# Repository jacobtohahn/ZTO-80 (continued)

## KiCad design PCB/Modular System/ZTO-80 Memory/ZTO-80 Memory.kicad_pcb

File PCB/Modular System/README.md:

## Modular System PCBs
The subfolders in this directory contain the KiCad project files and additional files for Modular System boards. Look in each subfolder for information on each board and files.

## Component Notes
Unless stated otherwise in a README or silkscreen, always use CMOS ICs to build your system.

To bridge jumpers, I recommend using standard 0.1 in. jumper shunts.

Please note that the 40-pin bus header uses a non-standard PCB footprint in my designs. This is to keep compatability with my older designs, which used the same footprint. The footprint still works with standard headers and isn't an issue unless you are making your own designs. To use this footprint, see the PCB design in the "ZTO-80 Template" subfolder.

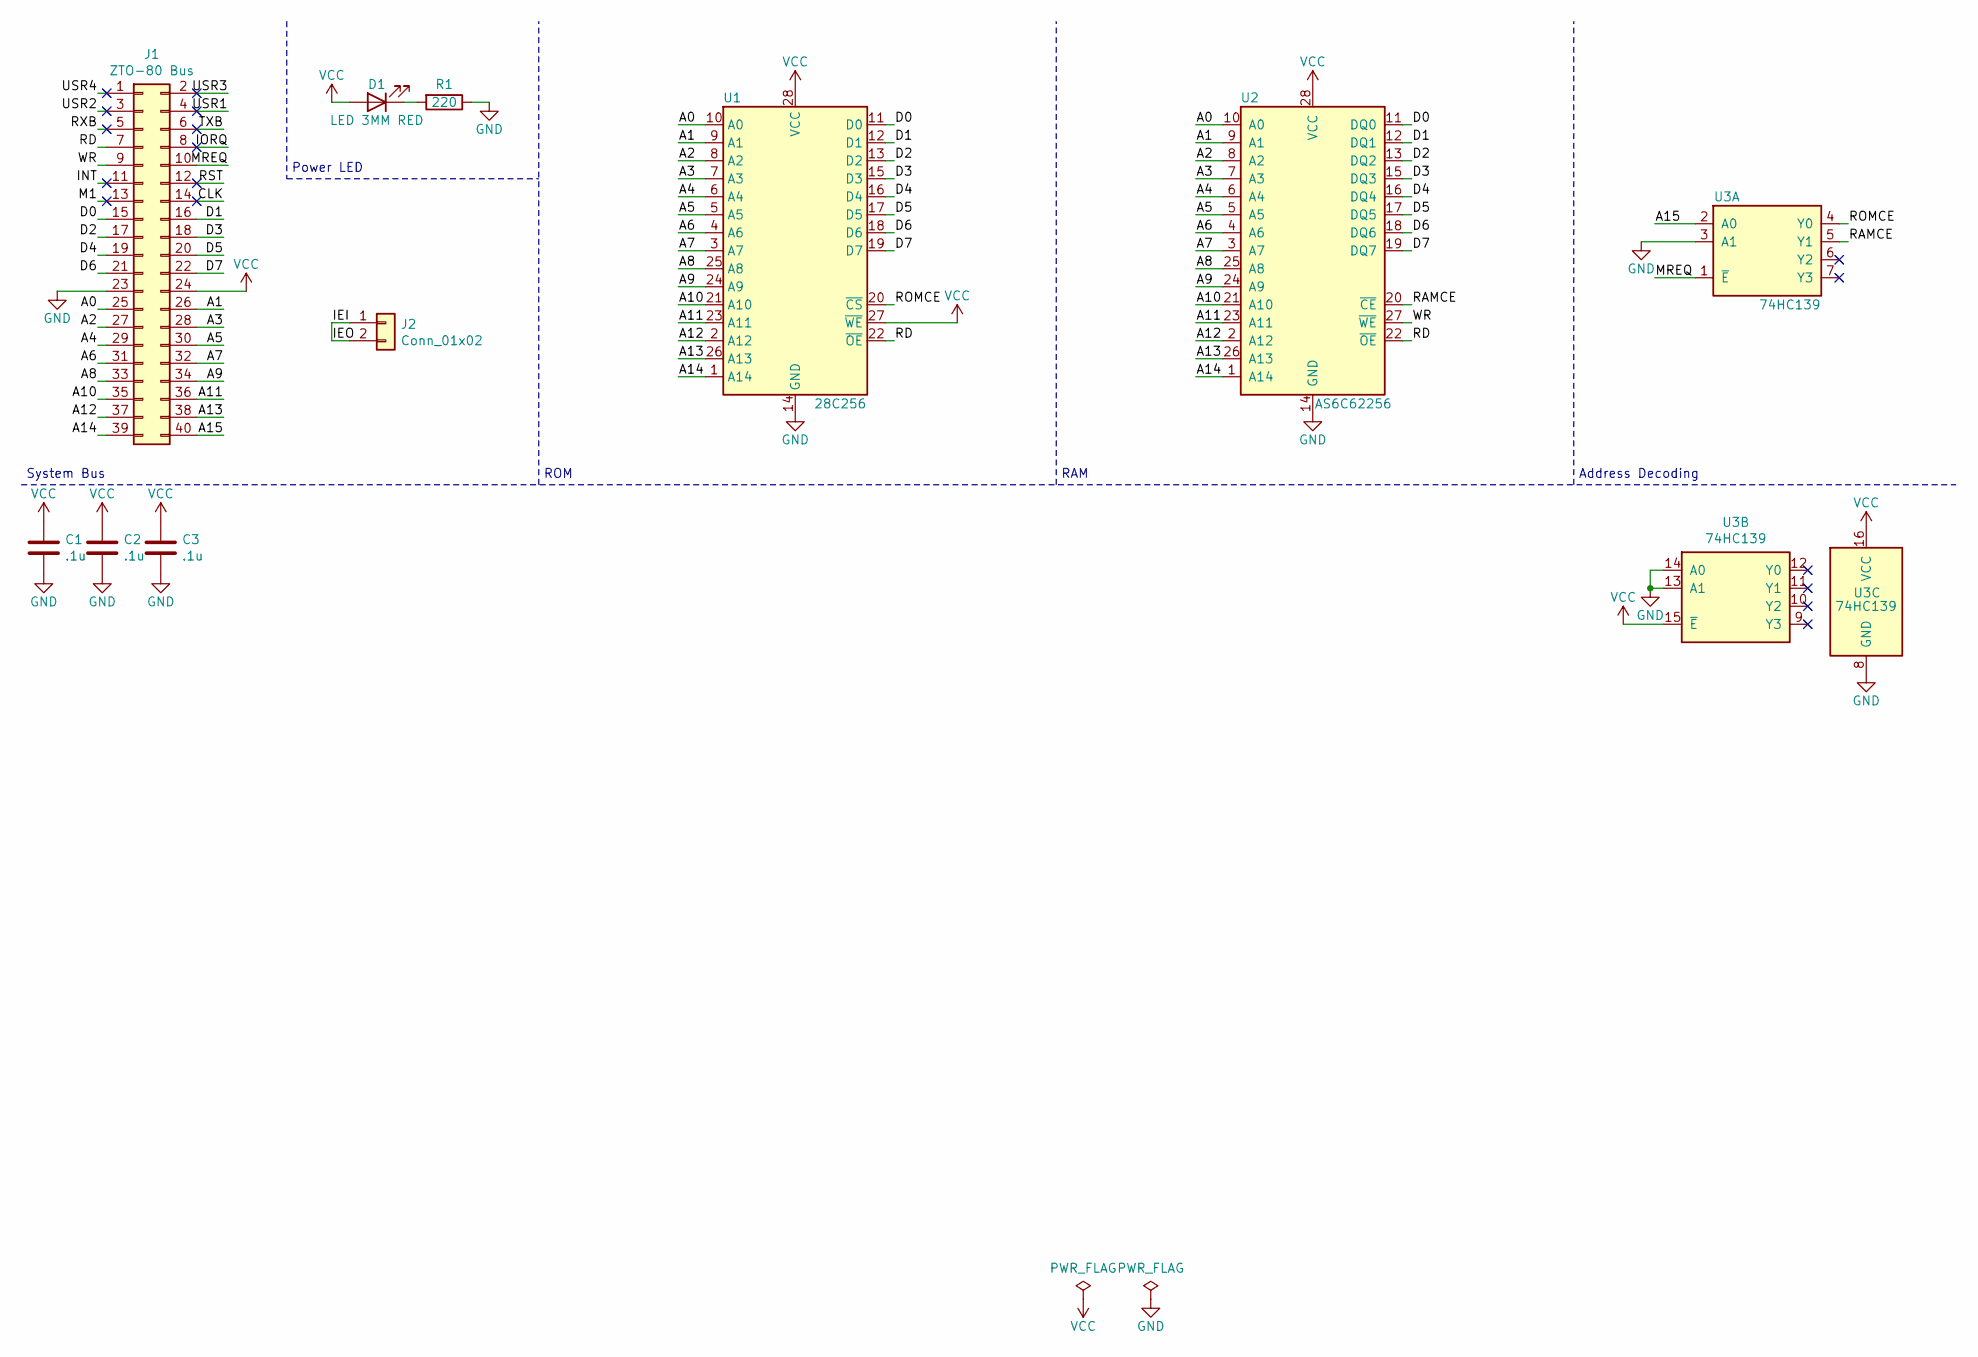
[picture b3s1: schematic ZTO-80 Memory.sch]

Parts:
C1, C2, C3: .1u; C_0805_2012Metric_Pad1.15x1.40mm_HandSolder
D1: LED 3MM RED; LED_D3.0mm
J1: ZTO-80 Bus; PinHeader_2x20_P2.54mm_Horizontal
J2: Conn_01x02; PinHeader_1x02_P2.54mm_Horizontal
R1: 220; R_0805_2012Metric_Pad1.15x1.40mm_HandSolder
U1: 28C256; DIP-28_W15.24mm
U2: AS6C62256; DIP-28_W15.24mm
U3: 74HC139; DIP-16_W7.62mm

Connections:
/A0: J1.25, U1.10 (A0), U2.10 (A0)
/A1: J1.26, U1.9 (A1), U2.9 (A1)
/A2: J1.27, U1.8 (A2), U2.8 (A2)
/A3: J1.28, U1.7 (A3), U2.7 (A3)
/A4: J1.29, U1.6 (A4), U2.6 (A4)
/A5: J1.30, U1.5 (A5), U2.5 (A5)
/A6: J1.31, U1.4 (A6), U2.4 (A6)
/A7: J1.32, U1.3 (A7), U2.3 (A7)
/A8: J1.33, U1.25 (A8), U2.25 (A8)
/A9: J1.34, U1.24 (A9), U2.24 (A9)
/A10: J1.35, U1.21 (A10), U2.21 (A10)
/A11: J1.36, U1.23 (A11), U2.23 (A11)
/A12: J1.37, U1.2 (A12), U2.2 (A12)
/A13: J1.38, U1.26 (A13), U2.26 (A13)
/A14: J1.39, U1.1 (A14), U2.1 (A14)
/A15: J1.40, U3.2 (A0)
/CLK: J1.14
/D0: J1.15, U1.11 (D0), U2.11 (DQ0)
/D1: J1.16, U1.12 (D1), U2.12 (DQ1)
/D2: J1.17, U1.13 (D2), U2.13 (DQ2)
/D3: J1.18, U1.15 (D3), U2.15 (DQ3)
/D4: J1.19, U1.16 (D4), U2.16 (DQ4)
/D5: J1.20, U1.17 (D5), U2.17 (DQ5)
/D6: J1.21, U1.18 (D6), U2.18 (DQ6)
/D7: J1.22, U1.19 (D7), U2.19 (DQ7)
/IEI: J2.1, J2.2
/INT: J1.11
/IORQ: J1.8
/M1: J1.13
/MREQ: J1.10, U3.1 (~E)
/RAMCE: U2.20 (~CE), U3.5 (Y1)
/RD: J1.7, U1.22 (~OE), U2.22 (~OE)
/ROMCE: U1.20 (~CS), U3.4 (Y0)
/RST: J1.12
/RXB: J1.5
/TXB: J1.6
/USR1: J1.4
/USR2: J1.3
/USR3: J1.2
/USR4: J1.1
/WR: J1.9, U2.27 (~WE)
GND: C1.2, C2.2, C3.2, J1.23, R1.1, U1.14 (GND), U2.14 (GND), U3.3 (A1), U3.8 (GND), U3.13 (A1), U3.14 (A0)
unnamed: D1.1 (K), R1.2
VCC: C1.1, C2.1, C3.1, D1.2 (A), J1.24, U1.27 (~WE), U1.28 (VCC), U2.28 (VCC), U3.15 (~E), U3.16 (VCC)

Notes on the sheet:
Power LED
System Bus
ROM
RAM
Address Decoding

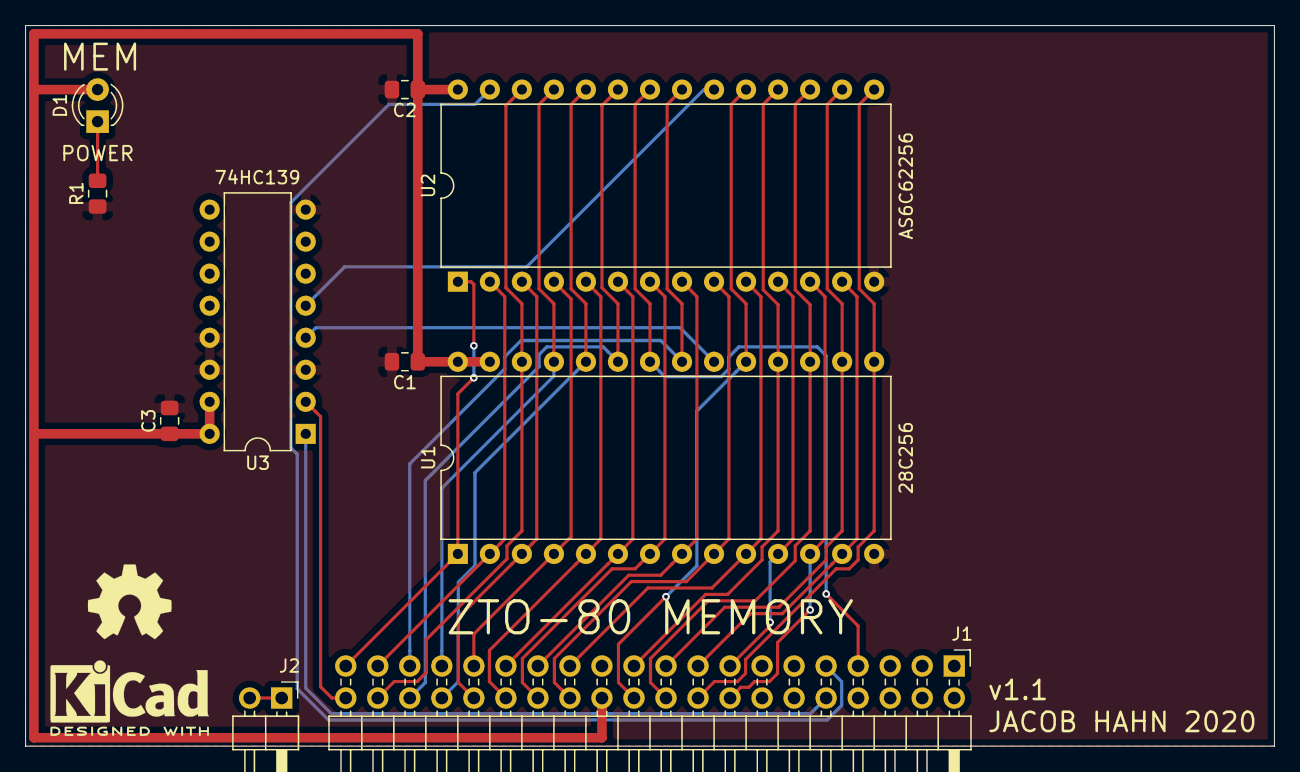
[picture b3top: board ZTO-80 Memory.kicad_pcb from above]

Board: 2 copper layers, 99.1 x 57.1 mm, 10 parts (0 on the bottom side), 33 nets.

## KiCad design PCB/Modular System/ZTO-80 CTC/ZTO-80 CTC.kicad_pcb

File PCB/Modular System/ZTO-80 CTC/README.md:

# ZTO-80 CTC
This is the CTC (Counter-Timer Circuit) board for the ZTO-80 Modular system. It contains the CTC, a DIP switch for setting the address, jumpers for setting the CTC configuration, and a pin header for outputting the CTC signals.

## Additional Files
- **PDF**: A subdirectory containing PDF files of the schematic and PCB.

## Component Notes
Use two pin male headers as the jumpers on this board.

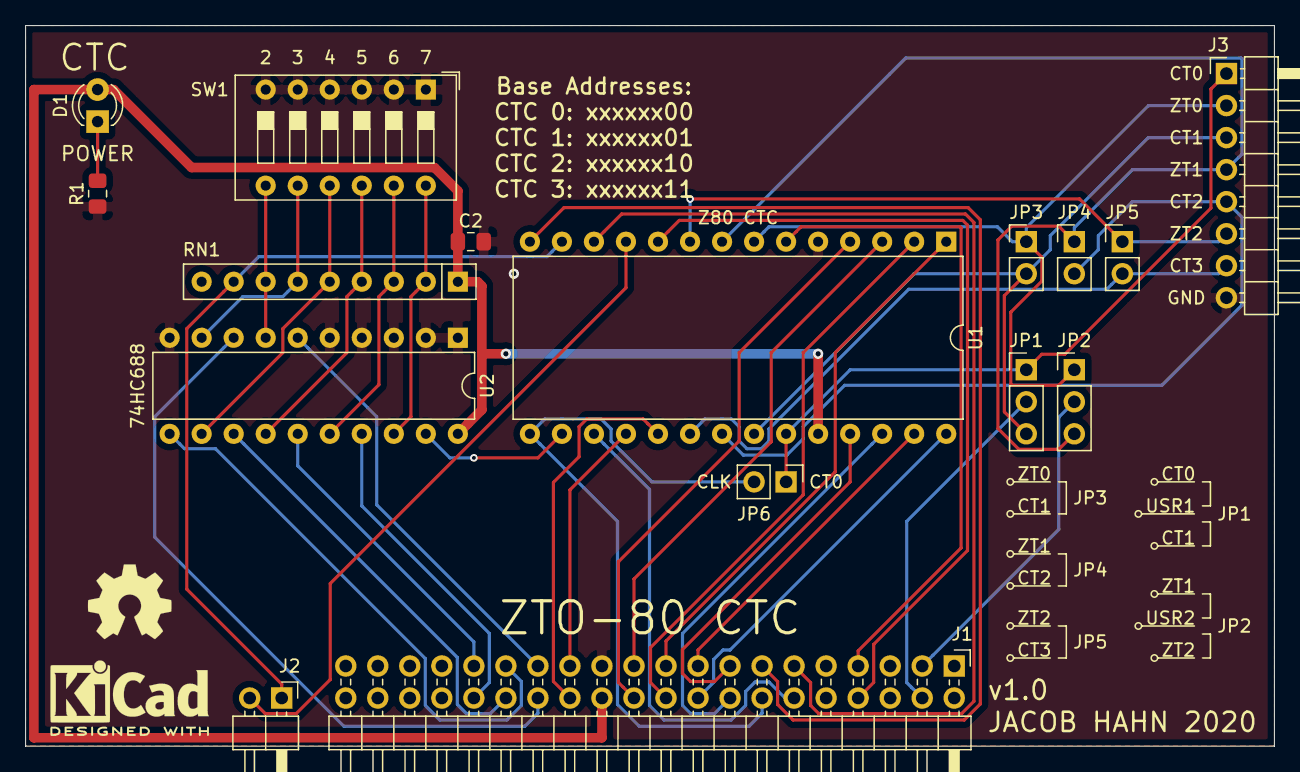
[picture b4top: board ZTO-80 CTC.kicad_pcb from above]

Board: 2 copper layers, 99.1 x 57.1 mm, 17 parts (1 on the bottom side), 43 nets.

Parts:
C1, C2: .1u; C_0805_2012Metric_Pad1.15x1.40mm_HandSolder
D1: LED 3MM RED; LED_D3.0mm
J1: ZTO-80 Bus; PinHeader_2x20_P2.54mm_Horizontal
J2: Conn_01x02; PinHeader_1x02_P2.54mm_Horizontal
J3: Conn_01x08; PinHeader_1x08_P2.54mm_Horizontal
JP1, JP2: Jumper_3_Open; PinHeader_1x03_P2.54mm_Vertical
JP3, JP4, JP5, JP6: Jumper_2_Open; PinHeader_1x02_P2.54mm_Vertical
R1: 220; R_0805_2012Metric_Pad1.15x1.40mm_HandSolder
RN1: 10k; R_Array_SIP9
SW1: SW_DIP_x06; SW_DIP_SPSTx06_Slide_9.78x17.42mm_W7.62mm_P2.54mm
U1: Z80CTC; DIP-28_W15.24mm
U2: 74HC688; DIP-20_W7.62mm

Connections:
/A0: J1.25, U1.18
/A1: J1.26, U1.19
/A2: J1.27, U2.6
/A3: J1.28, U2.8
/A4: J1.29, U2.11
/A5: J1.30, U2.13
/A6: J1.31, U2.15
/A7: J1.32, U2.17
/CLK: J1.14, JP6.2, U1.15
/CT0: J3.1, JP1.1, JP6.1, U1.23
/CT1: J3.3, JP1.3, JP3.2, U1.22
/CT2: J3.5, JP4.2, U1.21
/CT3: J3.7, JP5.2, U1.20
/CTCCE: U1.16, U2.19
/CTCIEI: J2.1, RN1.8, U1.13
/D0: J1.15, U1.25
/D1: J1.16, U1.26
/D2: J1.17, U1.27
/D3: J1.18, U1.28
/D4: J1.19, U1.1
/D5: J1.20, U1.2
/D6: J1.21, U1.3
/D7: J1.22, U1.4
/IEO: J2.2, U1.11
/INT: J1.11, U1.12
/IORQ: J1.8, U1.10
/M1: J1.13, U1.14
/RD: J1.7, U1.6
/RST: J1.12, U1.17
/SQ2: RN1.7, SW1.7, U2.7
/SQ3: RN1.6, SW1.8, U2.9
/SQ4: RN1.5, SW1.9, U2.12
/SQ5: RN1.4, SW1.10, U2.14
/SQ6: RN1.3, SW1.11, U2.16
/SQ7: RN1.2, SW1.12, U2.18
/USR1: J1.4, JP1.2
/USR2: J1.3, JP2.2
/ZT0: J3.2, JP2.1, JP3.1, U1.7
/ZT1: J3.4, JP2.3, JP4.1, U1.8
/ZT2: J3.6, JP5.1, U1.9
GND: C1.2, C2.2, J1.23, J3.8, R1.1, SW1.1, SW1.2, SW1.3, SW1.4, SW1.5, SW1.6, U1.5, U2.1, U2.2, U2.3, U2.4, U2.5, U2.10
unnamed: D1.1, R1.2
VCC: C1.1, C2.1, D1.2, J1.24, RN1.1, U1.24, U2.20

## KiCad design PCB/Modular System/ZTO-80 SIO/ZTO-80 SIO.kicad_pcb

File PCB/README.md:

# PCB
This directory contains the PCB files that I have created in KiCad so far, sorted as SBC PCBs and Modular System PCBs, along with any supporting documentation. The Modular System subdirectory contains a template for creating your own modules. See the READMEs in each subdirectory to get specific instructions for each board.

## Modular System Requirements
The three required boards for a working ZTO-80 Modular System are the Backplane, CPU board, and Memory board. Either the SIO or PIO board is required for output. The rest of the boards are optional and simply add additional features.

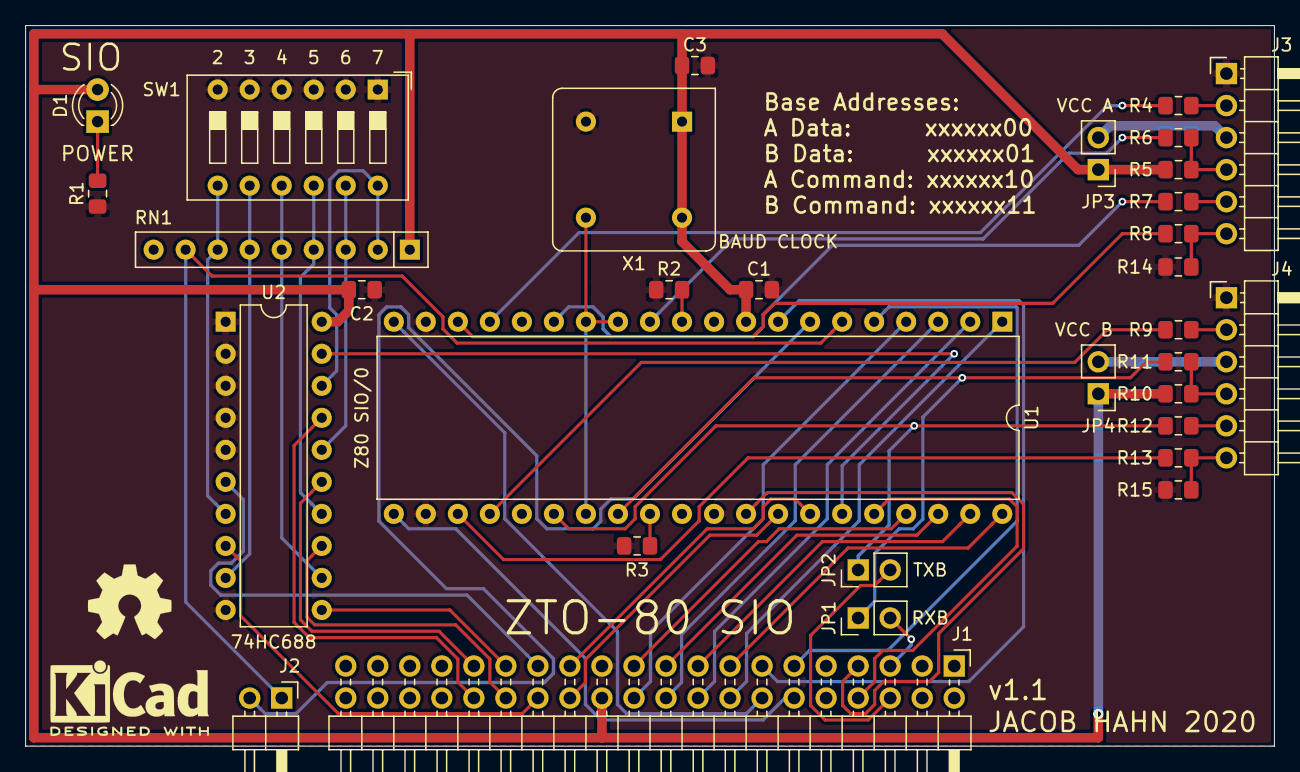
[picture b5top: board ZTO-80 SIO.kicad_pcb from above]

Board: 2 copper layers, 99.1 x 57.1 mm, 32 parts (0 on the bottom side), 57 nets.

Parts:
C1, C2, C3: .1u; C_0805_2012Metric_Pad1.15x1.40mm_HandSolder
D1: LED 3MM RED; LED_D3.0mm
J1: ZTO-80 Bus; PinHeader_2x20_P2.54mm_Horizontal
J2: Conn_01x02; PinHeader_1x02_P2.54mm_Horizontal
J3, J4: SIOHDR; PinHeader_1x06_P2.54mm_Horizontal
JP1, JP2: Jumper_NC_Small; PinHeader_1x02_P2.54mm_Vertical
JP3, JP4: Jumper_2_Open; PinHeader_1x02_P2.54mm_Vertical
R1: 220; R_0805_2012Metric_Pad1.15x1.40mm_HandSolder
R2, R3: 10k; R_0805_2012Metric_Pad1.15x1.40mm_HandSolder
R4, R6, R7, R8, R9, R11, R12, R13: 2.2k; R_0805_2012Metric_Pad1.15x1.40mm_HandSolder
R5, R10, R14, R15: 100k; R_0805_2012Metric_Pad1.15x1.40mm_HandSolder
RN1: R_Network08; R_Array_SIP9
SW1: SW_DIP_x06; SW_DIP_SPSTx06_Slide_9.78x17.42mm_W7.62mm_P2.54mm
U1: Z80SIO0; DIP-40_W15.24mm
U2: 74HC688; DIP-20_W7.62mm
X1: 1.8432MHz; Oscillator_DIP-8

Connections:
/A0: J1.25, U1.34
/A1: J1.26, U1.33
/A2: J1.27, U2.6
/A3: J1.28, U2.8
/A4: J1.29, U2.11
/A5: J1.30, U2.13
/A6: J1.31, U2.15
/A7: J1.32, U2.17
/BCLK: U1.13, U1.14, U1.27, X1.5
/CLK: J1.14, U1.20
/CTSA: R8.2, U1.18
/CTSB: R13.2, U1.23
/D0: J1.15, U1.40
/D1: J1.16, U1.1
/D2: J1.17, U1.39
/D3: J1.18, U1.2
/D4: J1.19, U1.38
/D5: J1.20, U1.3
/D6: J1.21, U1.37
/D7: J1.22, U1.4
/IEI: J2.1, RN1.8, U1.6
/IEO: J2.2, U1.7
/INT: J1.11, U1.5
/IORQ: J1.8, U1.36
/M1: J1.13, U1.8
/RD: J1.7, U1.32
/RST: J1.12, U1.21
/RTSA: R4.2, U1.17
/RTSB: R9.2, U1.24
/RXA: R6.2, U1.12
/RXB: JP1.1, R11.2, U1.28
/SIOCE: U1.35, U2.19
/TXA: R7.2, U1.15
/TXB: JP2.1, R12.2, U1.26
GND: C1.2, C2.2, C3.2, J1.23, J3.1, J4.1, R1.1, R2.1, R3.1, R14.1, R15.1, SW1.1, SW1.2, SW1.3, SW1.4, SW1.5, SW1.6, U1.19, U1.22, U1.31, U2.1, U2.2, U2.3, U2.4, U2.5, U2.10, X1.4
unnamed: D1.1, R1.2
unnamed: J1.5, JP1.2
unnamed: J1.6, JP2.2
unnamed: J3.2, R4.1
unnamed: J3.3, JP3.2
unnamed: J3.4, R5.1, R6.1
unnamed: J3.5, R7.1
unnamed: J3.6, R8.1, R14.2
unnamed: J4.2, R9.1
unnamed: J4.3, JP4.2
unnamed: J4.4, R10.1, R11.1
unnamed: J4.5, R12.1
unnamed: J4.6, R13.1, R15.2
unnamed: R2.2, U1.11
unnamed: R3.2, U1.29
unnamed: RN1.2, SW1.12, U2.18
unnamed: RN1.3, SW1.11, U2.16
unnamed: RN1.4, SW1.10, U2.14
unnamed: RN1.5, SW1.9, U2.12
unnamed: RN1.6, SW1.8, U2.9
unnamed: RN1.7, SW1.7, U2.7
VCC: C1.1, C2.1, C3.1, D1.2, J1.24, JP3.1, JP4.1, R5.2, R10.2, RN1.1, U1.9, U2.20, X1.1, X1.8

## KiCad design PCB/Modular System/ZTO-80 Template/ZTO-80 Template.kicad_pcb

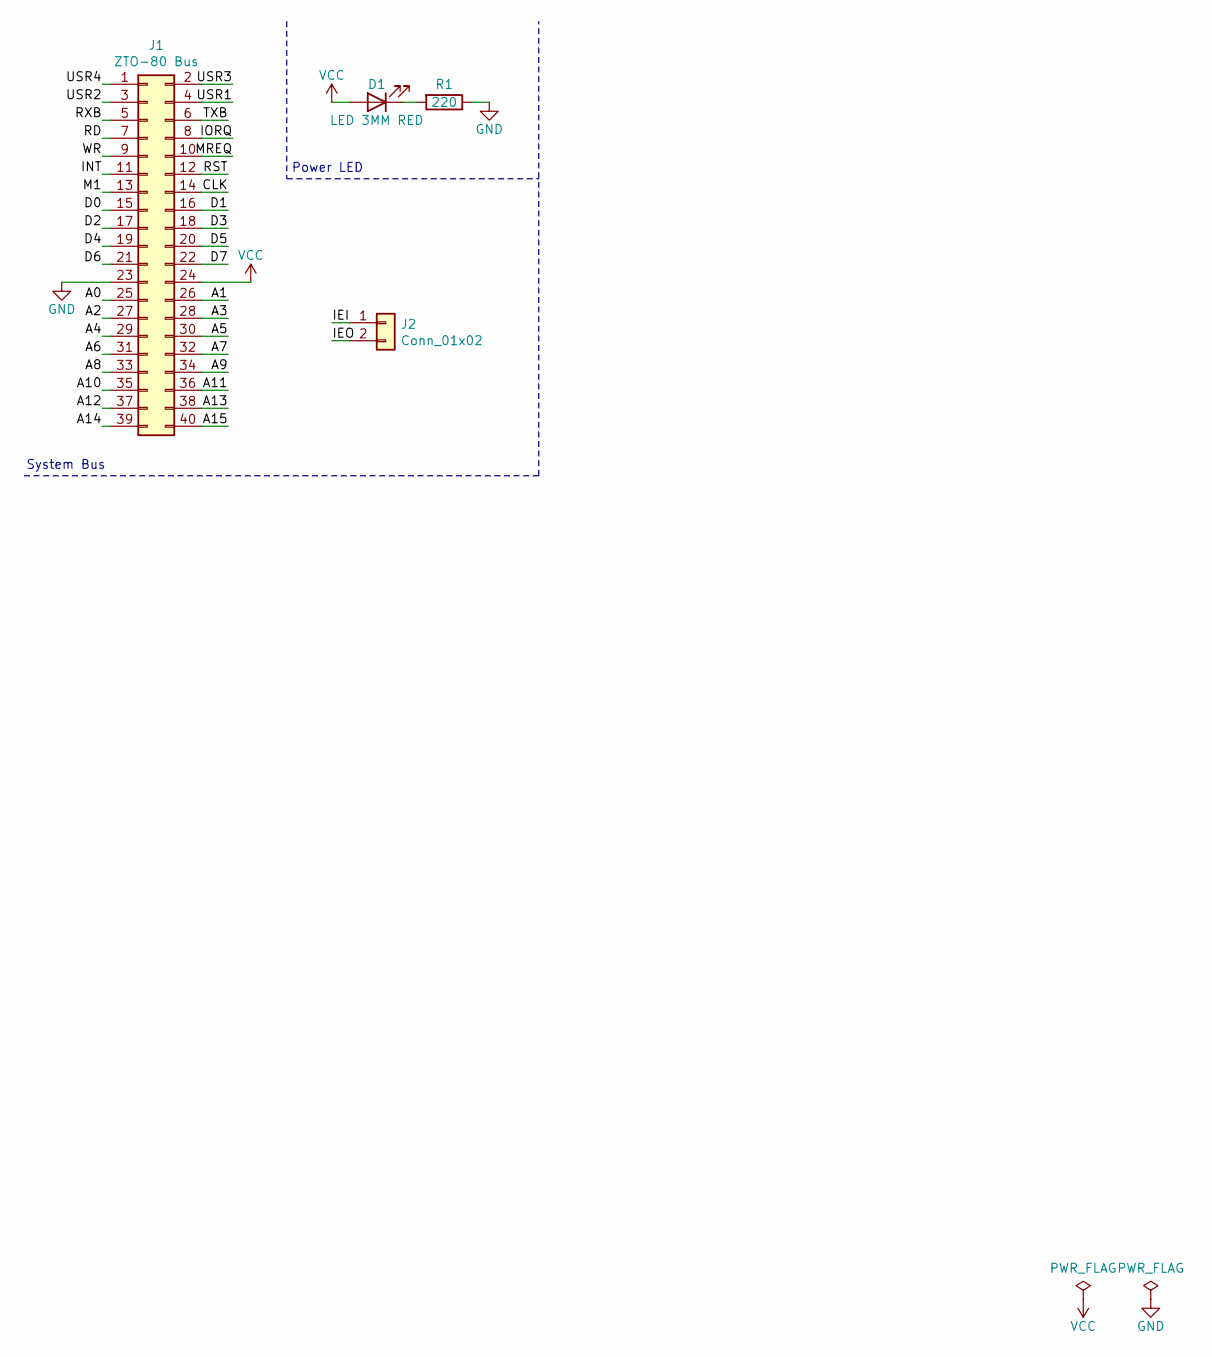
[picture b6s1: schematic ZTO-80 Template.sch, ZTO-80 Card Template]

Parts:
D1: LED 3MM RED; LED_D3.0mm
J1: ZTO-80 Bus; PinHeader_2x20_P2.54mm_Horizontal
J2: Conn_01x02; PinHeader_1x02_P2.54mm_Horizontal
R1: 220; R_0805_2012Metric_Pad1.15x1.40mm_HandSolder

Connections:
/A0: J1.25
/A1: J1.26
/A2: J1.27
/A3: J1.28
/A4: J1.29
/A5: J1.30
/A6: J1.31
/A7: J1.32
/A8: J1.33
/A9: J1.34
/A10: J1.35
/A11: J1.36
/A12: J1.37
/A13: J1.38
/A14: J1.39
/A15: J1.40
/CLK: J1.14
/D0: J1.15
/D1: J1.16
/D2: J1.17
/D3: J1.18
/D4: J1.19
/D5: J1.20
/D6: J1.21
/D7: J1.22
/IEI: J2.1
/IEO: J2.2
/INT: J1.11
/IORQ: J1.8
/M1: J1.13
/MREQ: J1.10
/RD: J1.7
/RST: J1.12
/RXB: J1.5
/TXB: J1.6
/USR1: J1.4
/USR2: J1.3
/USR3: J1.2
/USR4: J1.1
/WR: J1.9
GND: J1.23, R1.1
unnamed: D1.1 (K), R1.2
VCC: D1.2 (A), J1.24

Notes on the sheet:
Power LED
System Bus

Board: 2 copper layers, 4 parts (0 on the bottom side), 3 nets, no tracks yet.

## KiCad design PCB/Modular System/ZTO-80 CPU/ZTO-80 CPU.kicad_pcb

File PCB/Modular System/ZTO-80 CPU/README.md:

# ZTO-80 CPU
This is the CPU module for the ZTO-80 Modular System, containing the Z80 CPU, system clock, reset button, address and data buffers, and a header for CPU signals.

## Additional Files
- **PDF**: A subdirectory containing PDF files of the schematic and PCB.

## Component Notes
It is recommended to use a CMOS Z80 and 74HCT logic ICs on this board.

While Z80s overclock well, it is recommended that the max clock speed matches the CPU's rated speed.

Use two pin headers as jumpers on this board.

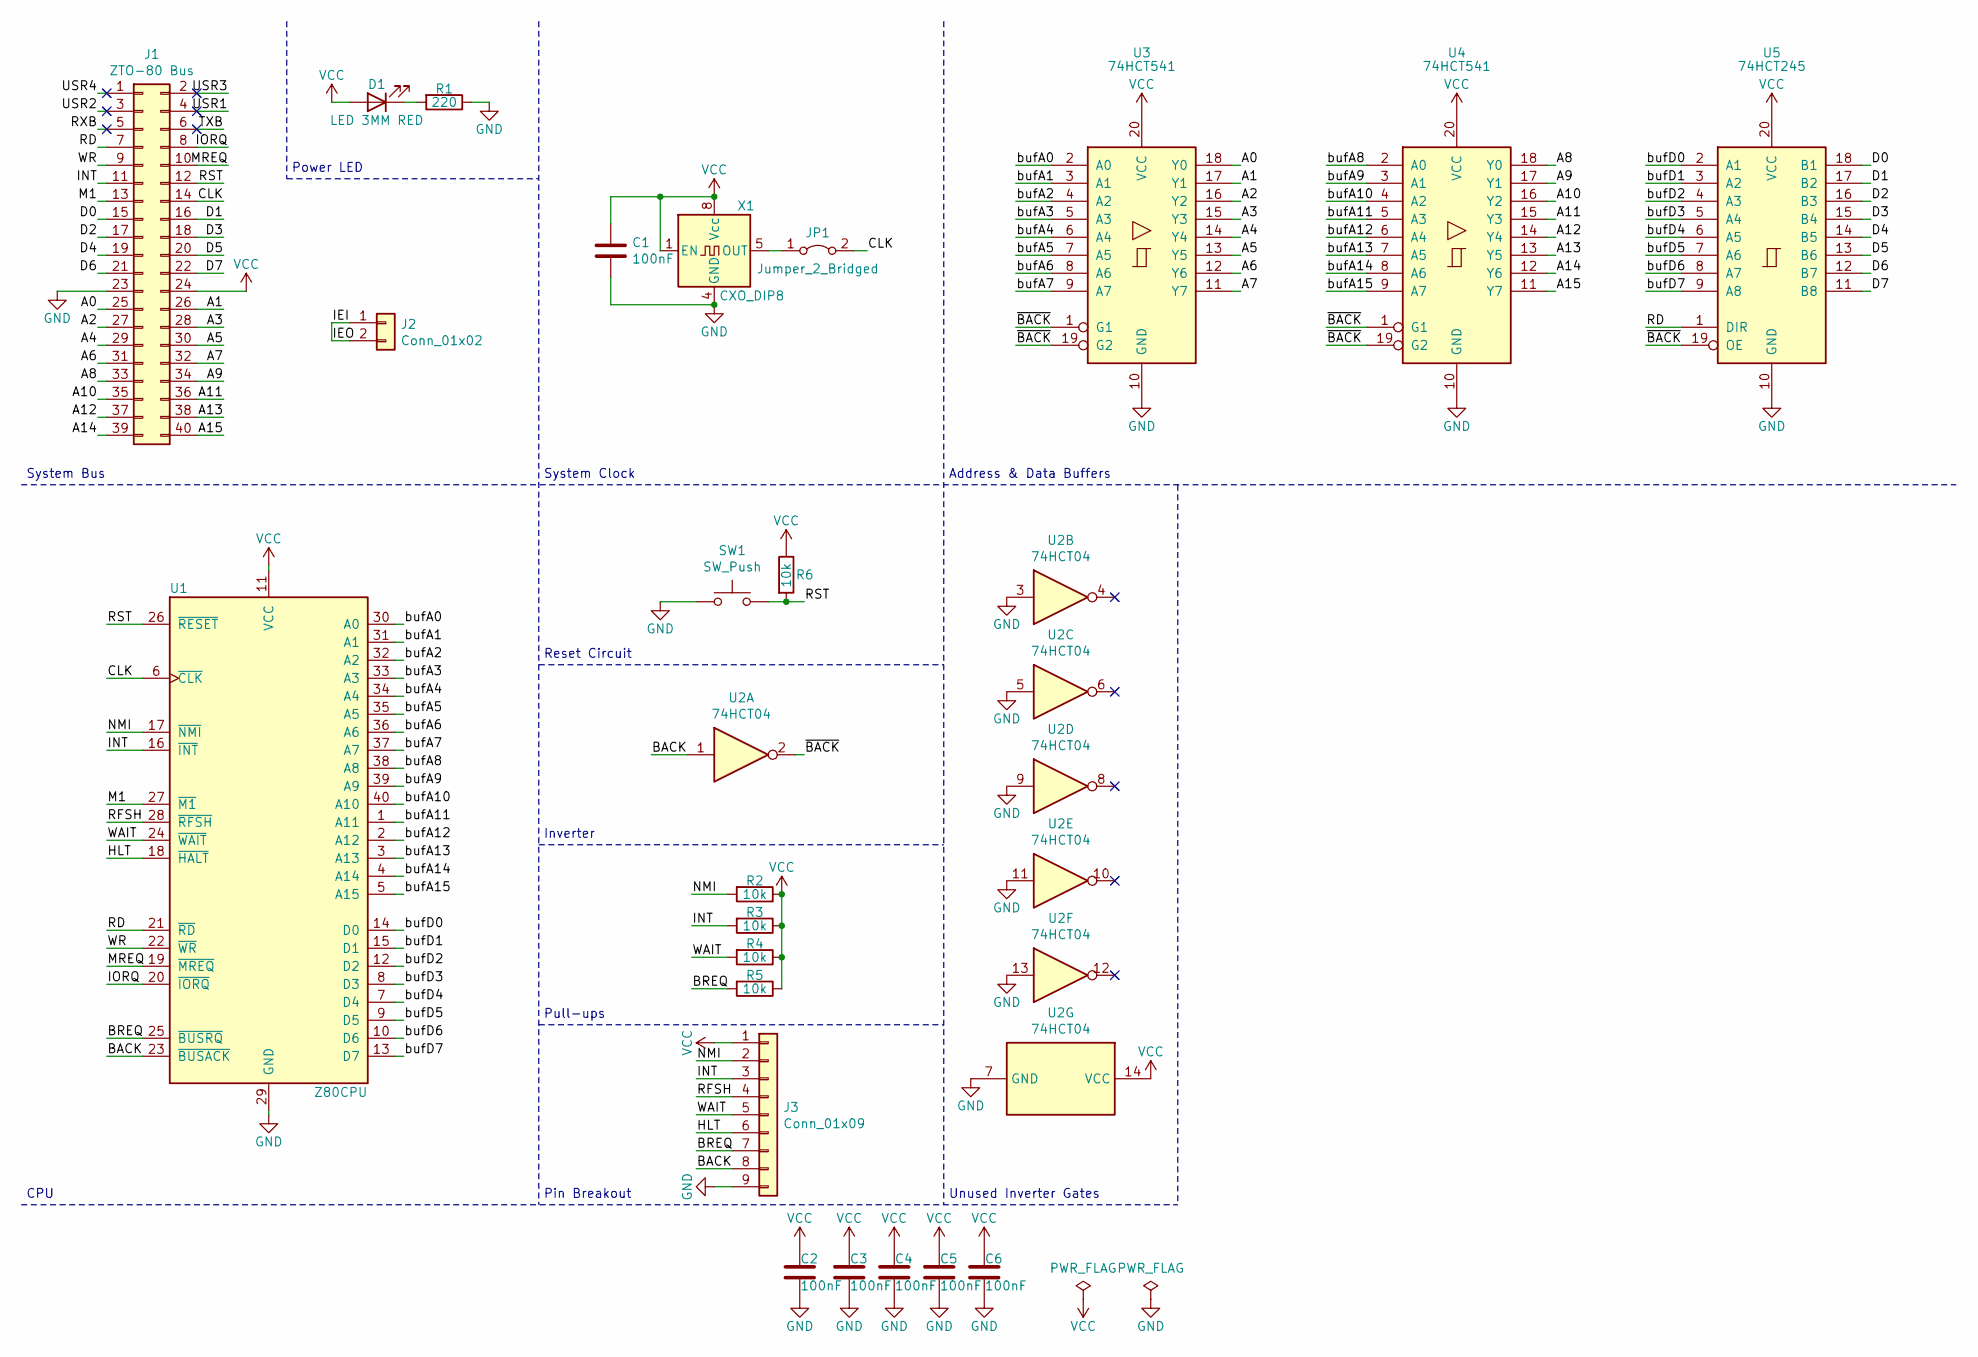
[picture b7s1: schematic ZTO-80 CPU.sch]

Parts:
C1, C2, C3, C4, C5, C6: 100nF; C_0805_2012Metric_Pad1.15x1.40mm_HandSolder
D1: LED 3MM RED; LED_D3.0mm
J1: ZTO-80 Bus; PinHeader_2x20_P2.54mm_Horizontal
J2: Conn_01x02; PinHeader_1x02_P2.54mm_Horizontal
J3: Conn_01x09; PinHeader_1x09_P2.54mm_Horizontal
JP1: Jumper_2_Bridged; PinHeader_1x02_P2.54mm_Vertical
R1: 220; R_0805_2012Metric_Pad1.15x1.40mm_HandSolder
R2, R3, R4, R5, R6: 10k; R_0805_2012Metric_Pad1.15x1.40mm_HandSolder
SW1: SW_Push; SW_PUSH_6mm
U1: Z80CPU; DIP-40_W15.24mm
U2: 74HCT04; DIP-14_W7.62mm
U3, U4: 74HCT541; DIP-20_W7.62mm
U5: 74HCT245; DIP-20_W7.62mm
X1: CXO_DIP8; Oscillator_DIP-8

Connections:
/A0: J1.25, U3.18 (Y0)
/A1: J1.26, U3.17 (Y1)
/A2: J1.27, U3.16 (Y2)
/A3: J1.28, U3.15 (Y3)
/A4: J1.29, U3.14 (Y4)
/A5: J1.30, U3.13 (Y5)
/A6: J1.31, U3.12 (Y6)
/A7: J1.32, U3.11 (Y7)
/A8: J1.33, U4.18 (Y0)
/A9: J1.34, U4.17 (Y1)
/A10: J1.35, U4.16 (Y2)
/A11: J1.36, U4.15 (Y3)
/A12: J1.37, U4.14 (Y4)
/A13: J1.38, U4.13 (Y5)
/A14: J1.39, U4.12 (Y6)
/A15: J1.40, U4.11 (Y7)
/BACK: J3.8, U1.23 (~BUSACK~), U2.1
/BREQ: J3.7, R5.2, U1.25 (~BUSRQ~)
/CLK: J1.14, JP1.2 (B), U1.6 (~CLK~)
/D0: J1.15, U5.18 (B1)
/D1: J1.16, U5.17 (B2)
/D2: J1.17, U5.16 (B3)
/D3: J1.18, U5.15 (B4)
/D4: J1.19, U5.14 (B5)
/D5: J1.20, U5.13 (B6)
/D6: J1.21, U5.12 (B7)
/D7: J1.22, U5.11 (B8)
/HLT: J3.6, U1.18 (~HALT~)
/IEI: J2.1, J2.2
/INT: J1.11, J3.3, R3.2, U1.16 (~INT~)
/IORQ: J1.8, U1.20 (~IORQ~)
/M1: J1.13, U1.27 (~M1~)
/MREQ: J1.10, U1.19 (~MREQ~)
/NMI: J3.2, R2.2, U1.17 (~NMI~)
/RD: J1.7, U1.21 (~RD~), U5.1 (DIR)
/RFSH: J3.4, U1.28 (~RFSH~)
/RST: J1.12, R6.2, SW1.2, U1.26 (~RESET~)
/RXB: J1.5
/TXB: J1.6
/USR1: J1.4
/USR2: J1.3
/USR3: J1.2
/USR4: J1.1
/WAIT: J3.5, R4.2, U1.24 (~WAIT~)
/WR: J1.9, U1.22 (~WR~)
/bufA0: U1.30 (A0), U3.2 (A0)
/bufA1: U1.31 (A1), U3.3 (A1)
/bufA2: U1.32 (A2), U3.4 (A2)
/bufA3: U1.33 (A3), U3.5 (A3)
/bufA4: U1.34 (A4), U3.6 (A4)
/bufA5: U1.35 (A5), U3.7 (A5)
/bufA6: U1.36 (A6), U3.8 (A6)
/bufA7: U1.37 (A7), U3.9 (A7)
/bufA8: U1.38 (A8), U4.2 (A0)
/bufA9: U1.39 (A9), U4.3 (A1)
/bufA10: U1.40 (A10), U4.4 (A2)
/bufA11: U1.1 (A11), U4.5 (A3)
/bufA12: U1.2 (A12), U4.6 (A4)
/bufA13: U1.3 (A13), U4.7 (A5)
/bufA14: U1.4 (A14), U4.8 (A6)
/bufA15: U1.5 (A15), U4.9 (A7)
/bufD0: U1.14 (D0), U5.2 (A1)
/bufD1: U1.15 (D1), U5.3 (A2)
/bufD2: U1.12 (D2), U5.4 (A3)
/bufD3: U1.8 (D3), U5.5 (A4)
/bufD4: U1.7 (D4), U5.6 (A5)
/bufD5: U1.9 (D5), U5.7 (A6)
/bufD6: U1.10 (D6), U5.8 (A7)
/bufD7: U1.13 (D7), U5.9 (A8)
/~BACK: U2.2, U3.1 (G1), U3.19 (G2), U4.1 (G1), U4.19 (G2), U5.19 (OE)
GND: C1.2, C2.2, C3.2, C4.2, C5.2, C6.2, J1.23, J3.9, R1.1, SW1.1, U1.29 (GND), U2.3, U2.5, U2.7 (GND), U2.9, U2.11, U2.13, U3.10 (GND), U4.10 (GND), U5.10 (GND), X1.4 (GND)
unnamed: D1.1 (K), R1.2
unnamed: JP1.1 (A), X1.5 (OUT)
VCC: C1.1, C2.1, C3.1, C4.1, C5.1, C6.1, D1.2 (A), J1.24, J3.1, R2.1, R3.1, R4.1, R5.1, R6.1, U1.11 (VCC), U2.14 (VCC), U3.20 (VCC), U4.20 (VCC), U5.20 (VCC), X1.1 (EN), X1.8 (Vcc)

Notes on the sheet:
Power LED
System Bus
System Clock
CPU
Address & Data Buffers
Inverter
Reset Circuit
Pull-ups
Unused Inverter Gates
Pin Breakout

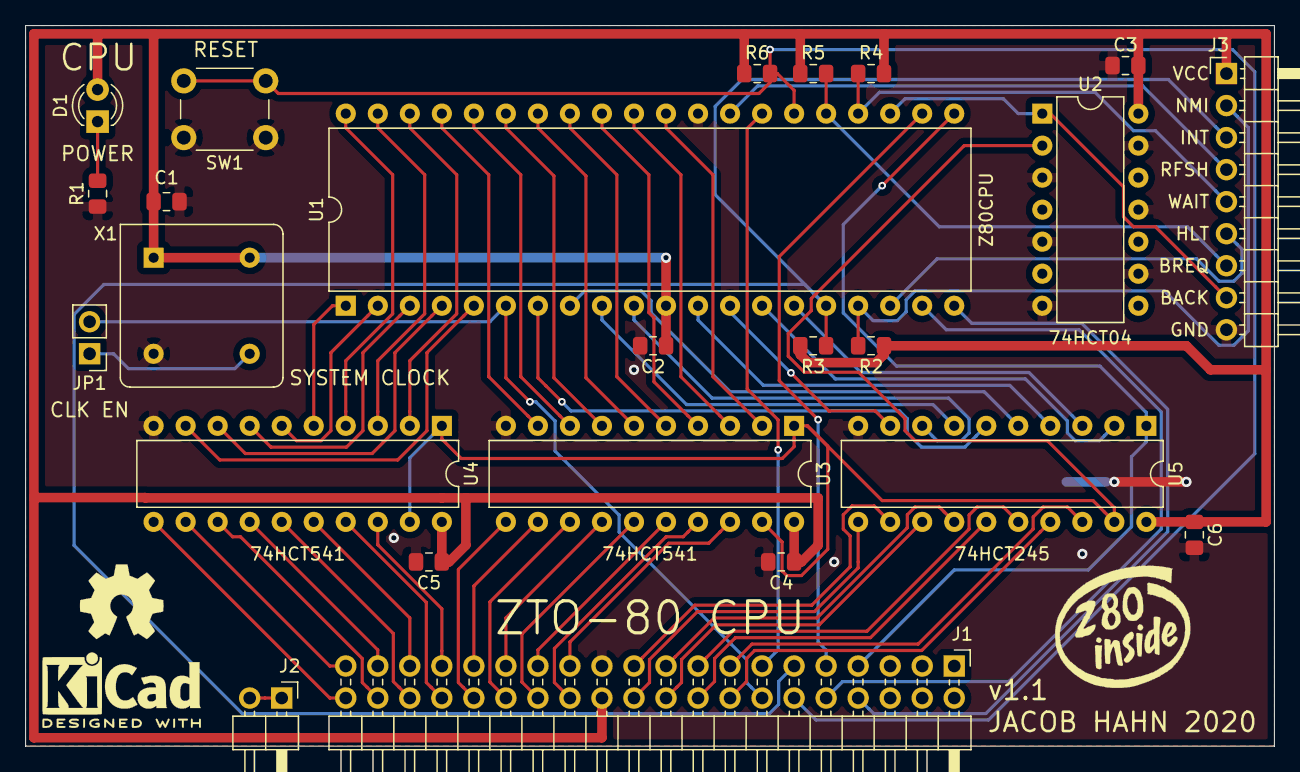
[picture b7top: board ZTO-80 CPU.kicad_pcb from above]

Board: 2 copper layers, 99.1 x 57.1 mm, 24 parts (0 on the bottom side), 68 nets.

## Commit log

2020-08-01 BASIC code
2020-08-01 Added code
2020-08-02 Organized code
2020-08-02 Compile asm
2020-08-02 Update code readme
2020-08-02 Edit code README
2020-08-02 Fixed errors in int32k.asm
2020-08-02 Added PCB files and updated READMEs
2020-08-03 Edited power LED resistor value
2020-08-03 Add PDFs
2020-08-06 Added images
2020-08-08 Added PDFs and datasheets
2020-08-11 Added SBC
2020-08-11 Fixed RTS/CTS handshaking
2020-08-11 Revert "Fixed RTS/CTS handshaking"
    This reverts commit 626e7b437206d130b4d22168190954aac9009a2b.
2020-08-11 Deleted unnecessary PCB files
2020-08-11 Edit READMEs
2020-08-12 Added module template README
2020-08-14 Updates to PDFs and the SBC
2020-08-14 Update issue templates
2020-08-14 Added version info to BASIC startup
2020-08-14 Added SBC Guide
2020-08-14 Update README to reflect added documentation
2020-08-14 Removed template PDFs
2020-08-16 Net name update for SBC
2020-08-16 Added component note to Modular System README
2020-08-17 Removed obsolete info from README
2020-08-17 Changed bus orientation
    This change is backwards-compatible with all previous ZTO-80 modules
2020-08-17 Created ZTO-80 SIO
2020-08-17 Update LICENSE
2020-08-17 Create LICENSE
2020-08-17 Added CERN license how-to
2020-08-17 Added license to README
2020-08-17 Added CERN license text to silkscreen
2020-08-18 Updated SBC and added releases folder
2020-08-21 Added documentation license
2020-08-29 Add details to README
2020-08-29 Added contact info to README
2020-09-01 Updated SBC to v3.1
2020-09-01 Release v1.0.0
2020-09-05 Add info about modular system
2020-09-05 Renamed photo
2020-09-05 Changes to BASIC README
2020-09-20 Small changes to SBC
2020-09-21 Add documentation to SBC
2020-10-02 Reworded code attribution
2020-10-02 Finished SIO
2020-10-02 Finished Backplane
2020-10-02 Added photos
2020-10-03 Finished CTC
2020-10-04 Finished Memory
2020-10-04 Finished CPU
2020-10-08 Updated Backplane
2020-10-09 Updated SBC photo in README
2020-12-21 Updated readme to reflect latest design
2021-03-17 Updated documentation to Edition 1.4
2021-05-20 SBC Getting Started Guide 1.5
2021-05-20 Preparing directory structure for SBC v3.2
2021-05-20 Renamed files to differentiate versions
2021-05-20 Add SBC v3.2 files
2021-05-20 Add info to README
2021-09-26 Changed SBC V3.2 files and added PDFs
2021-09-26 Add feature request issue template
2023-02-27 Updates to 3.2 and SBC Backplane
2023-02-27 Create SBC PDF warning
